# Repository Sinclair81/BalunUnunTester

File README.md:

# Balun Unun Tester v2

<!-- markdownlint-disable MD033 -->

<!-- markdownlint-enable MD033 -->

Heavily inspired by the [Balun / UnUn Tester XXL](https://funkfieber.com/Balun-UnUn-Tester-V3-XXL.html) by DO1HFS - Heinrich - [www.funkfieber.com](www.funkfieber.com)  

Balun / UnUn ([UniBalun](https://github.com/DG1JAN/UniBalun)) by DG1JAN - Jan - [radiosocial.de/@DG1JAN](https://radiosocial.de/@DG1JAN)  

The design of the sOTA adapter is based on the [sOTA-Antenna](https://github.com/DG1JAN/xOTA-Antenna) from DG1JAN - Jan

<!-- markdownlint-disable MD033 -->

<!-- markdownlint-enable MD033 -->

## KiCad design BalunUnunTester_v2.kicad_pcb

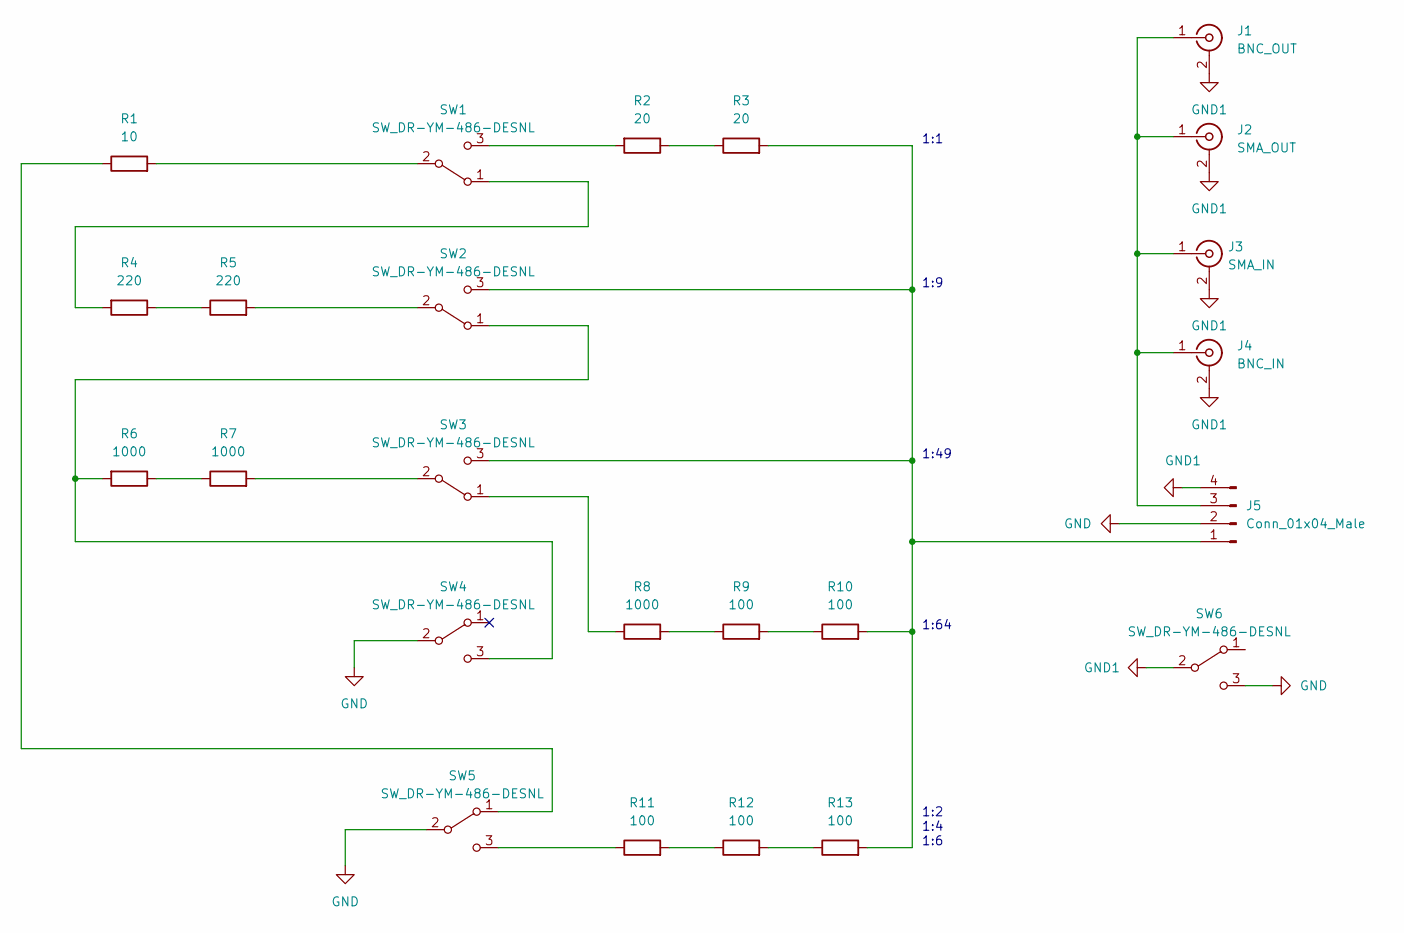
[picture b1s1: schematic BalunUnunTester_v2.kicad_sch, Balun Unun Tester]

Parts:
J1: BNC_OUT; BNC_Amphenol_B6252HB-NPP3G-50_Horizontal
J2: SMA_OUT; SMA_Molex_73251-2200_Horizontal_neu
J3: SMA_IN; SMA_Molex_73251-2200_Horizontal_neu
J4: BNC_IN; BNC_Amphenol_B6252HB-NPP3G-50_Horizontal
J5: Conn_01x04_Male; PinHeader_1x04_P2.54mm_Horizontal
R1: 10; R_Axial_DIN0414_L11.9mm_D4.5mm_P15.24mm_Horizontal
R2, R3: 20; R_Axial_DIN0414_L11.9mm_D4.5mm_P15.24mm_Horizontal
R4, R5: 220; R_Axial_DIN0414_L11.9mm_D4.5mm_P15.24mm_Horizontal
R6, R7, R8: 1000; R_Axial_DIN0414_L11.9mm_D4.5mm_P15.24mm_Horizontal
R9, R10, R11, R12, R13: 100; R_Axial_DIN0414_L11.9mm_D4.5mm_P15.24mm_Horizontal
SW1, SW2, SW3, SW4, SW5, SW6: SW_DR-YM-486-DESNL

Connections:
GND: J5.2, SW4.2 (B), SW5.2 (B), SW6.3 (C)
GND1: J1.2 (Ext), J2.2 (Ext), J3.2 (Ext), J4.2 (Ext), J5.4, SW6.2 (B)
unnamed: J1.1 (In), J2.1 (In), J3.1 (In), J4.1 (In), J5.3
unnamed: R1.1, SW5.1 (A)
unnamed: R1.2, SW1.2 (B)
unnamed: R2.1, R3.1
unnamed: R2.2, SW1.3 (C)
unnamed: R4.1, R5.1
unnamed: R4.2, SW1.1 (A)
unnamed: R5.2, SW2.2 (B)
unnamed: R6.1, R7.1
unnamed: R6.2, SW2.1 (A), SW4.3 (C)
unnamed: R7.2, SW3.2 (B)
unnamed: R8.1, SW3.1 (A)
unnamed: R8.2, R9.1
unnamed: R9.2, R10.1
unnamed: J5.1, R3.2, R10.2, R13.2, SW2.3 (C), SW3.3 (C)
unnamed: R11.1, SW5.3 (C)
unnamed: R11.2, R12.1
unnamed: R12.2, R13.1

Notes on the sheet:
1:64
1:49
1:9
1:1
1:2 1:4 1:6

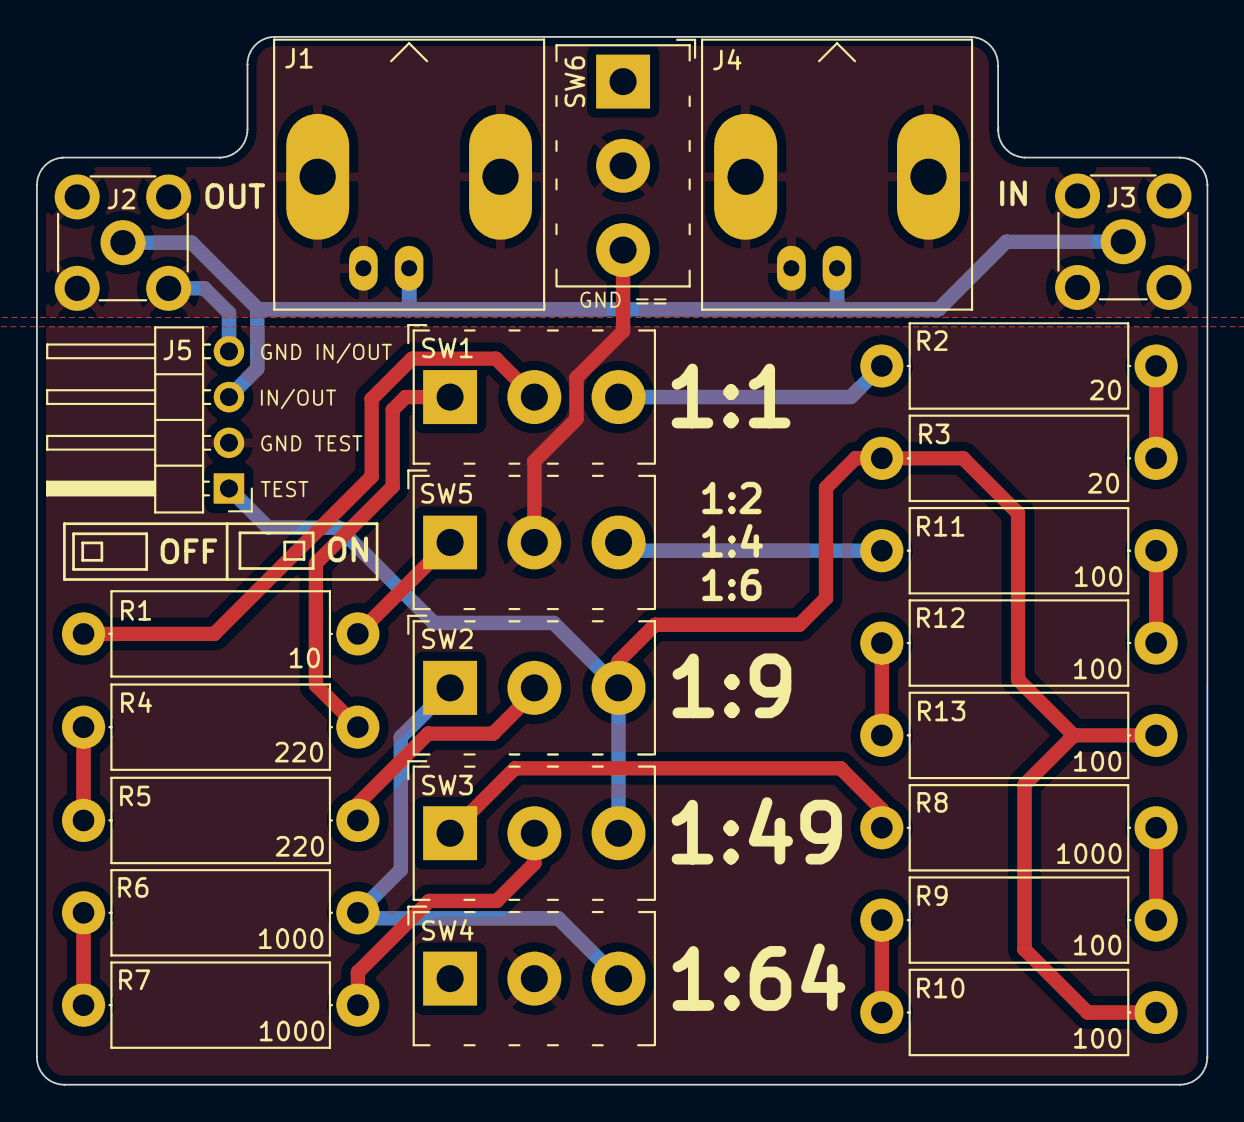
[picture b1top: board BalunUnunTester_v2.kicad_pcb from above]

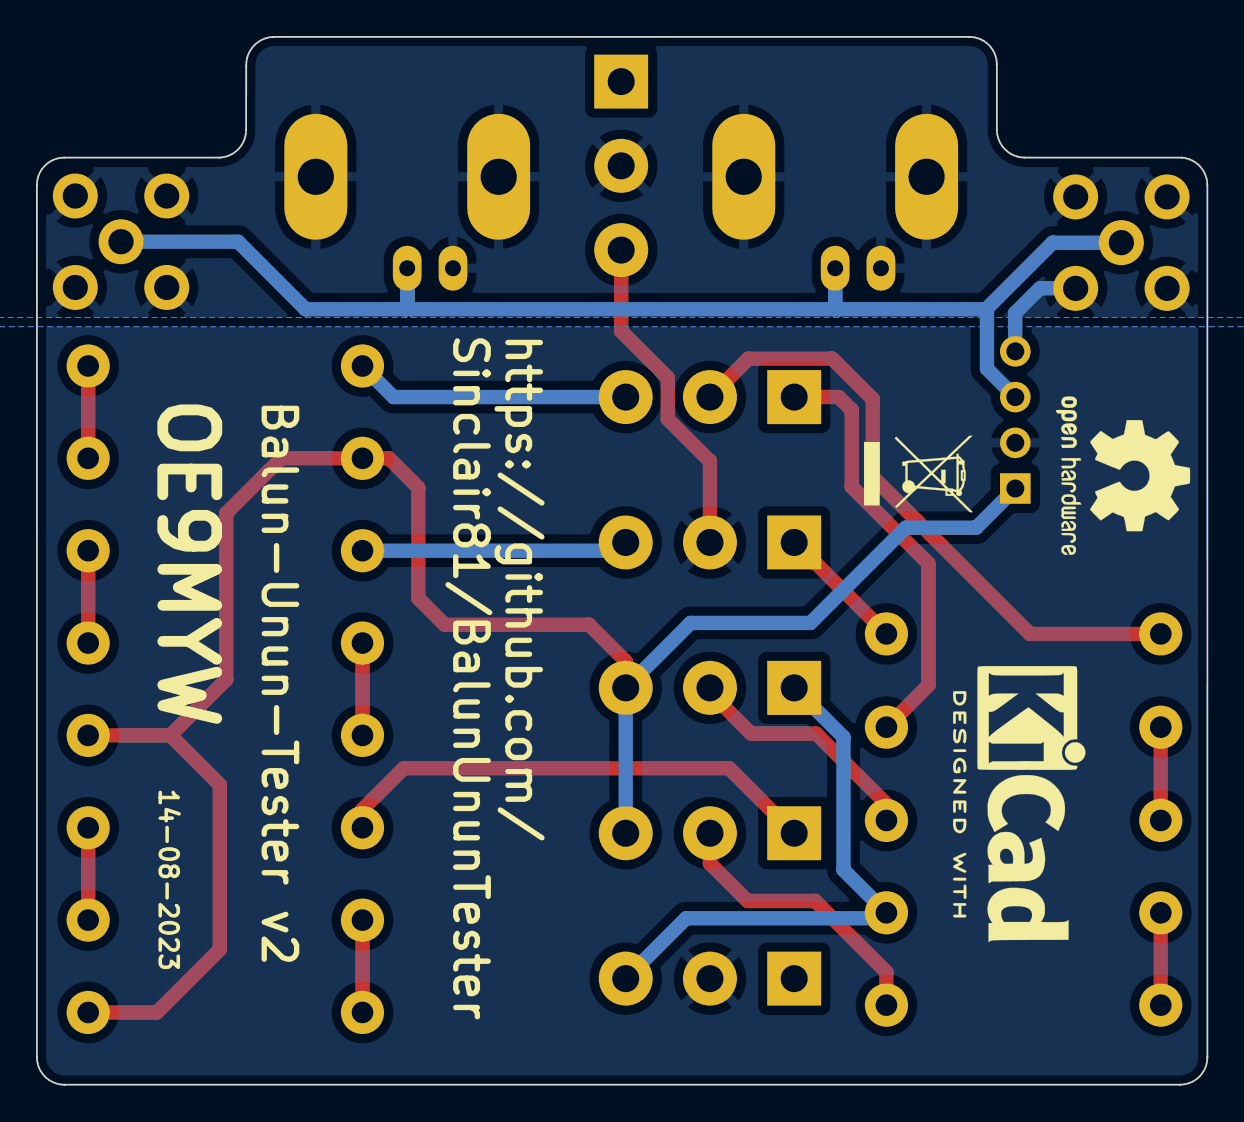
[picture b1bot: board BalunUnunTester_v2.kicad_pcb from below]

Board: 2 copper layers, 65.0 x 58.2 mm, 27 parts (3 on the bottom side), 20 nets.

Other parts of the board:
REF1: KiCad-Logo2_6mm_SilkScreen
REF2: OSHW-Logo2_9.8x8mm_SilkScreen
REF3: WEEE-Logo_4.2x6mm_SilkScreen

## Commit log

2023-08-14 Init
2023-08-14 Add Files
2023-08-31 Add xOTA Adapter STL
2023-09-03 Add UniBalun_2_xOTA_Adapter
2023-10-24 change stl's
